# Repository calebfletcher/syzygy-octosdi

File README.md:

# syzygy-octosdi

SYZYGY™ TXR4 Compatible 3G-SDI Pod, with quad inputs and quad outputs.

Compatible with the SYZYGY Specification Version 1.1.1. The "SYZYGY™" mark is owned by Opal Kelly.

## Features
- SYZYGY TXR4 Pod
- 4x 3D-SDI inputs and 4x 3G-SDI outputs, all independent
- Full-size BNC connectors
- TI LMH0344 Cable Equalizers
- Semtech GS2988 Cable Drivers
- Lock/Signal Present LEDs at each BNC
- 148.5MHz oscillator on REFCLK
- I2C I/O expanders for all driver/equalizer control and status signals
- SmartVIO STM32G031 microcontroller with ability to measure VIO voltage

## Limitations
- Only 3G-SDI is supported
- There is no 148.5/1.001 MHz oscillator support
  - The board has only been designed for fractional framerates to keep the design a bit simpler. Depending on your FPGA, there may be enough tolerance on the MGT PLL to allow fractional rate inputs to be received despite it not being the correct frequency. This is the case at least for Xilinx Ultrascale+ GTYs with a +/-1250 ppm tolerance. However, this will not work for the transmitters which require the exact frequency.
- No reclockers on the board. It is designed to be plugged directly into an FPGA so this likely has no impact on its use.

## BOM Substitutions
While this board has been designed to use LMH0344 for the cable EQs and GS2988 for the cable drivers, there is broad compatibility across Semtech and TIs SDI portfolio. As such, some unpopulated footprints are available for passives needed for one chip or another, in particular for replacing the GS2988 with a LMH0302. See TI's SNLA280 for a full list of available substitutes for cable drivers, and SNLA283 for cable equalizers.

## [Interactive BOM](https://html-preview.github.io/?url=https://github.com/calebfletcher/syzygy-octosdi/blob/main/docs/ibom.html)

## Ordering Details
Designed to meet JLCPCBs standard capabilities.

Four layers, 1.6 mm, 1 oz outer/0.5 oz inner, JLC04161H-7628 stackup, controlled impedance.

## SYZYGY Compatibility Table

Following the pod compatibility table in [Appendix A of the SYZYGY Specification Version 1.1.1](https://syzygyfpga.io/wp-content/uploads/2023/09/Syzygy-Specification-V1p1p1.pdf):

| Parameter | syzygy-octosdi |
|-----------|----------------|
| Type | SYZYGY Transceiver (TXR-4) |
| Maximum 5V supply current | 0 mA |
| Maximum 3.3V supply current | 1.2 A (provisional design budget) |
| VIO supply voltage(s) | 1.8 V, 2.5 V, or 3.3 V |
| Maximum VIO supply current | 10 mA (provisional design budget) |
| Total number of I/O | 4 single-ended (S0–S3) |
| Number of differential I/O pairs (Standard pod only) | N/A (TXR-4 pod) |
| Transceiver lanes | 4 RX and 4 TX, plus REFCLK input |
| Width | Single |

The current budgets are conservative estimates from the schematic and component specifications; they have not been verified by measurement. The 5V pin is routed only to a test point. VIO powers the I/O side of the two expanders and the control-signal pull-ups.

## SYZYGY Pinout
Pinout for CN1 (QTH-020-01-F-D-DP-A):

| Pin number | Pin name      | Pin net      |
|------------|---------------|--------------|
| 01         | SCL\_01       | VIO\_I2C.SCL |
| 02         | +5V\_02       | +5V          |
| 03         | SDA\_03       | VIO\_I2C.SDA |
| 04         | R\_GA\_04     | R\_GA        |
| 05         | RX0P\_05      | RX0.P        |
| 06         | TX0P\_06      | TX0.P        |
| 07         | RX0N\_07      | RX0.N        |
| 08         | TX0N\_08      | TX0.N        |
| 09         | RX1P\_09      | RX1.P        |
| 10         | TX1P\_10      | TX1.P        |
| 11         | RX1N\_11      | RX1.N        |
| 12         | TX1N\_12      | TX1.N        |
| 13         | REFCLKP\_13   | REFCLK.P     |
| 14         | S0\_14        | I2C.SCL      |
| 15         | REFCLKN\_15   | REFCLK.N     |
| 16         | S1\_16        | I2C.SDA      |
| 17         | S2\_17        | ~{RESET}     |
| 18         | S3\_18        | ~{INT}       |
| 19         | S4\_19        | NC           |
| 20         | S5\_20        | NC           |
| 21         | S6\_21        | NC           |
| 22         | S7\_22        | NC           |
| 23         | S8\_23        | NC           |
| 24         | S9\_24        | NC           |
| 25         | RX3P\_25      | RX3.P        |
| 26         | TX3P\_26      | TX3.P        |
| 27         | RX3N\_27      | RX3.N        |
| 28         | TX3N\_28      | TX3.N        |
| 29         | RX2P\_29      | RX2.P        |
| 30         | TX2P\_30      | TX2.P        |
| 31         | RX2N\_31      | RX2.N        |
| 32         | TX2N\_32      | TX2.N        |
| 33         | P2C\_CLKP\_33 | NC           |
| 34         | C2P\_CLKP\_34 | NC           |
| 35         | P2C\_CLKN\_35 | NC           |
| 36         | C2P\_CLKN\_36 | NC           |
| 37         | RSVD\_37      | NC           |
| 38         | RSVD\_38      | NC           |
| 39         | VIO1\_39      | VIO          |
| 40         | +3.3V\_40     | +3V3         |
| G1         | GND\_G1       | GND          |
| G2         | GND\_G2       | GND          |
| G3         | GND\_G3       | GND          |
| G4         | GND\_G4       | GND          |

## SmartVIO STM32 Pinout
Pinout for U11 (STM32G031G8Ux):

| Pin number | Pin name       | Pin net               |
|------------|----------------|-----------------------|
| 1          | PC14\_1        | NC                    |
| 2          | PC15\_2        | NC                    |
| 3          | VDD\_3         | +3V3                  |
| 4          | VSS\_4         | GND                   |
| 5          | PF2\_5         | SmartVIO/NRST         |
| 6          | ADC1\_IN0\_6   | R\_GA                 |
| 7          | ADC1\_IN1\_7   | VIO                   |
| 8          | PA2\_8         | VIO\_GOOD             |
| 9          | PA3\_9         | ~{VIO\_GOOD}          |
| 10         | PA4\_10        | NC                    |
| 11         | PA5\_11        | NC                    |
| 12         | PA6\_12        | NC                    |
| 13         | PA7\_13        | NC                    |
| 14         | PB0\_14        | Net-(U11-PB0)         |
| 15         | PB1\_15        | Net-(U11-PB1)         |
| 16         | PA8\_16        | NC                    |
| 17         | PC6\_17        | NC                    |
| 18         | PA9/PA11\_18   | NC                    |
| 19         | PA10/PA12\_19  | NC                    |
| 20         | SYS\_SWDIO\_20 | SmartVIO/SWDIO        |
| 21         | SYS\_SWCLK\_21 | SmartVIO/SWCLK        |
| 22         | PA15\_22       | NC                    |
| 23         | PB3\_23        | NC                    |
| 24         | PB4\_24        | SmartVIO/USER\_LED\_0 |
| 25         | PB5\_25        | SmartVIO/USER\_LED\_1 |
| 26         | I2C1\_SCL\_26  | VIO\_I2C.SCL          |
| 27         | I2C1\_SDA\_27  | VIO\_I2C.SDA          |
| 28         | PB8\_28        | NC                    |

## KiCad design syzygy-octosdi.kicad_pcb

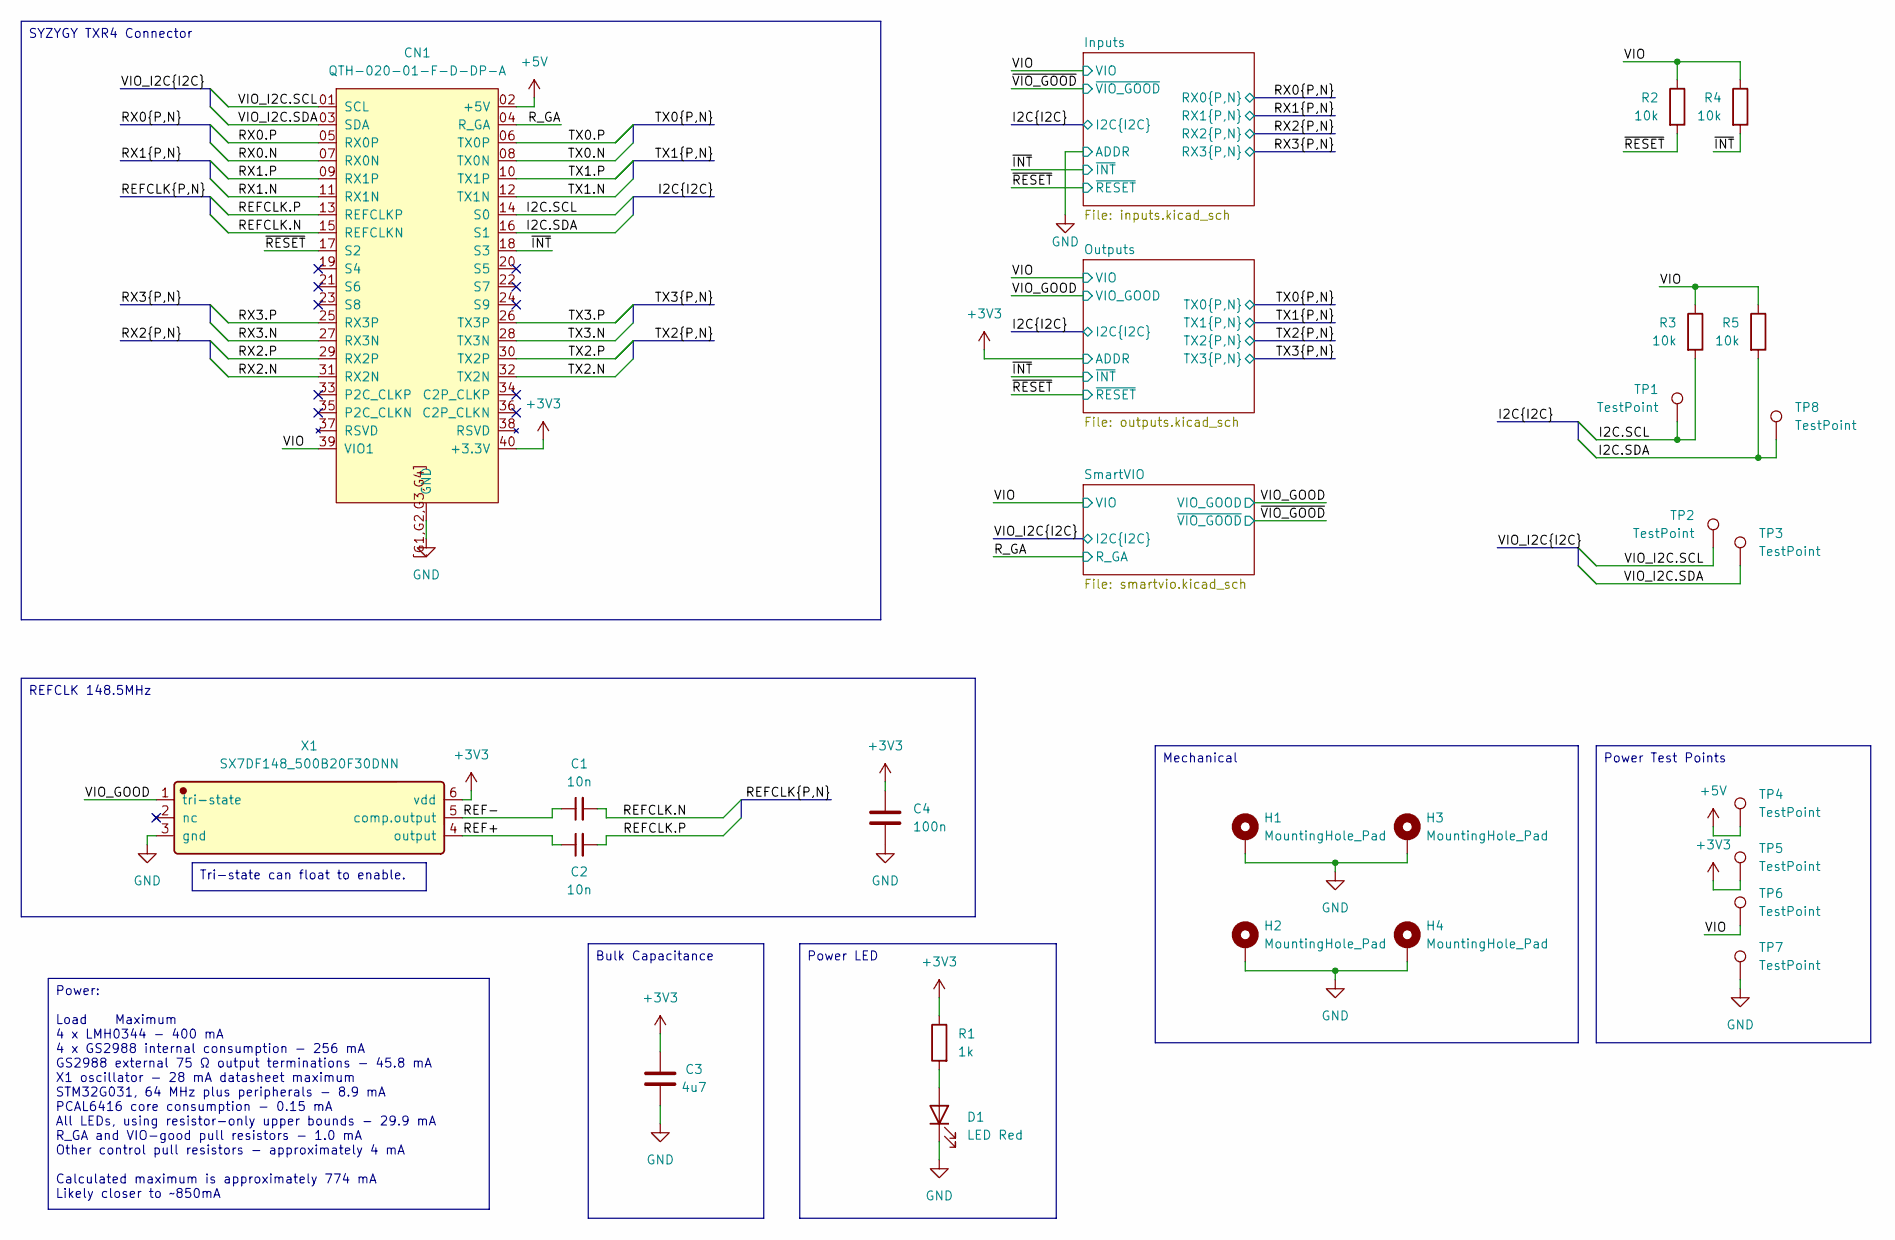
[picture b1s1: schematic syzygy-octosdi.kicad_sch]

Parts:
C1, C2: 10n; C_0402_1005Metric; LCSC C15195
C3: 4u7; C_0603_1608Metric; LCSC C69335
C4: 100n; C_0603_1608Metric; LCSC C282519
CN1: QTH-020-01-F-D-DP-A; Manufacturer Part QTH-020-01-F-D-DP-A; LCSC C5852101
D1: LED Red; LED_0603_1608Metric; LCSC C965799
H1, H2, H3, H4: MountingHole_Pad; MountingHole_3.2mm_M3_Pad
R1: 1k; R_0603_1608Metric; LCSC C21190
R2, R3, R4, R5: 10k; R_0603_1608Metric; LCSC C25804
TP1, TP2, TP3, TP4, TP5, TP6, TP7, TP8: TestPoint; TestPoint_Pad_D1.0mm
X1: SX7DF148_500B20F30DNN; Manufacturer Part SX7DF148.500B20F30DNN; LCSC C5179986

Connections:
+3V3: C3.1, C4.1, CN1.40 (+3.3V), R1.1, TP5.1 (1_1), X1.6 (vdd); also elsewhere on the board
+5V: CN1.02 (+5V), TP4.1 (1_1)
/I2C.SCL: CN1.14 (S0), R3.2, TP1.1 (1_1); also elsewhere on the board
/I2C.SDA: CN1.16 (S1), R5.2, TP8.1 (1_1); also elsewhere on the board
/REF+: C2.1, X1.4 (output)
/REF-: C1.1, X1.5 (comp.output)
/REFCLK.N: C1.2, CN1.15 (REFCLKN)
/REFCLK.P: C2.2, CN1.13 (REFCLKP)
/RX0.N: CN1.07 (RX0N); also elsewhere on the board
/RX0.P: CN1.05 (RX0P); also elsewhere on the board
/RX1.N: CN1.11 (RX1N); also elsewhere on the board
/RX1.P: CN1.09 (RX1P); also elsewhere on the board
/RX2.N: CN1.31 (RX2N); also elsewhere on the board
/RX2.P: CN1.29 (RX2P); also elsewhere on the board
/RX3.N: CN1.27 (RX3N); also elsewhere on the board
/RX3.P: CN1.25 (RX3P); also elsewhere on the board
/R_GA: CN1.04 (R_GA); also elsewhere on the board
/TX0.N: CN1.08 (TX0N); also elsewhere on the board
/TX0.P: CN1.06 (TX0P); also elsewhere on the board
/TX1.N: CN1.12 (TX1N); also elsewhere on the board
/TX1.P: CN1.10 (TX1P); also elsewhere on the board
/TX2.N: CN1.32 (TX2N); also elsewhere on the board
/TX2.P: CN1.30 (TX2P); also elsewhere on the board
/TX3.N: CN1.28 (TX3N); also elsewhere on the board
/TX3.P: CN1.26 (TX3P); also elsewhere on the board
/VIO: CN1.39 (VIO1), R2.1, R3.1, R4.1, R5.1, TP6.1 (1_1); also elsewhere on the board
/VIO_GOOD: X1.1 (tri-state); also elsewhere on the board
/VIO_I2C.SCL: CN1.01 (SCL), TP2.1 (1_1); also elsewhere on the board
/VIO_I2C.SDA: CN1.03 (SDA), TP3.1 (1_1); also elsewhere on the board
/~INT: CN1.18 (S3), R4.2; also elsewhere on the board
/~RESET: CN1.17 (S2), R2.2; also elsewhere on the board
GND: C3.2, C4.2, CN1.G1 (GND), CN1.G2 (GND), CN1.G3 (GND), CN1.G4 (GND), CN1.[G1,G2,G3,G4] (GND), D1.1 (K), H1.1 (1_1), H2.1 (1_1), H3.1 (1_1), H4.1 (1_1), TP7.1 (1_1), X1.3 (gnd); also elsewhere on the board
unnamed: D1.2 (A), R1.2

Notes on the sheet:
Power: Load Maximum 4 x LMH0344 - 400 mA 4 x GS2988 internal consumption - 256 mA GS2988 external 75 Ω output terminations - 45.8 mA X1 oscillator - 28 mA datasheet maximum STM32G031, 64 MHz plus peripherals - 8.9 mA PCAL6416 core consumption - 0.15 mA All LEDs, using resistor-only upper bounds - 2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
Mechanical
SYZYGY TXR4 Connector
Power Test Points
REFCLK 148.5MHz
Bulk Capacitance
Tri-state can float to enable.
Power LED

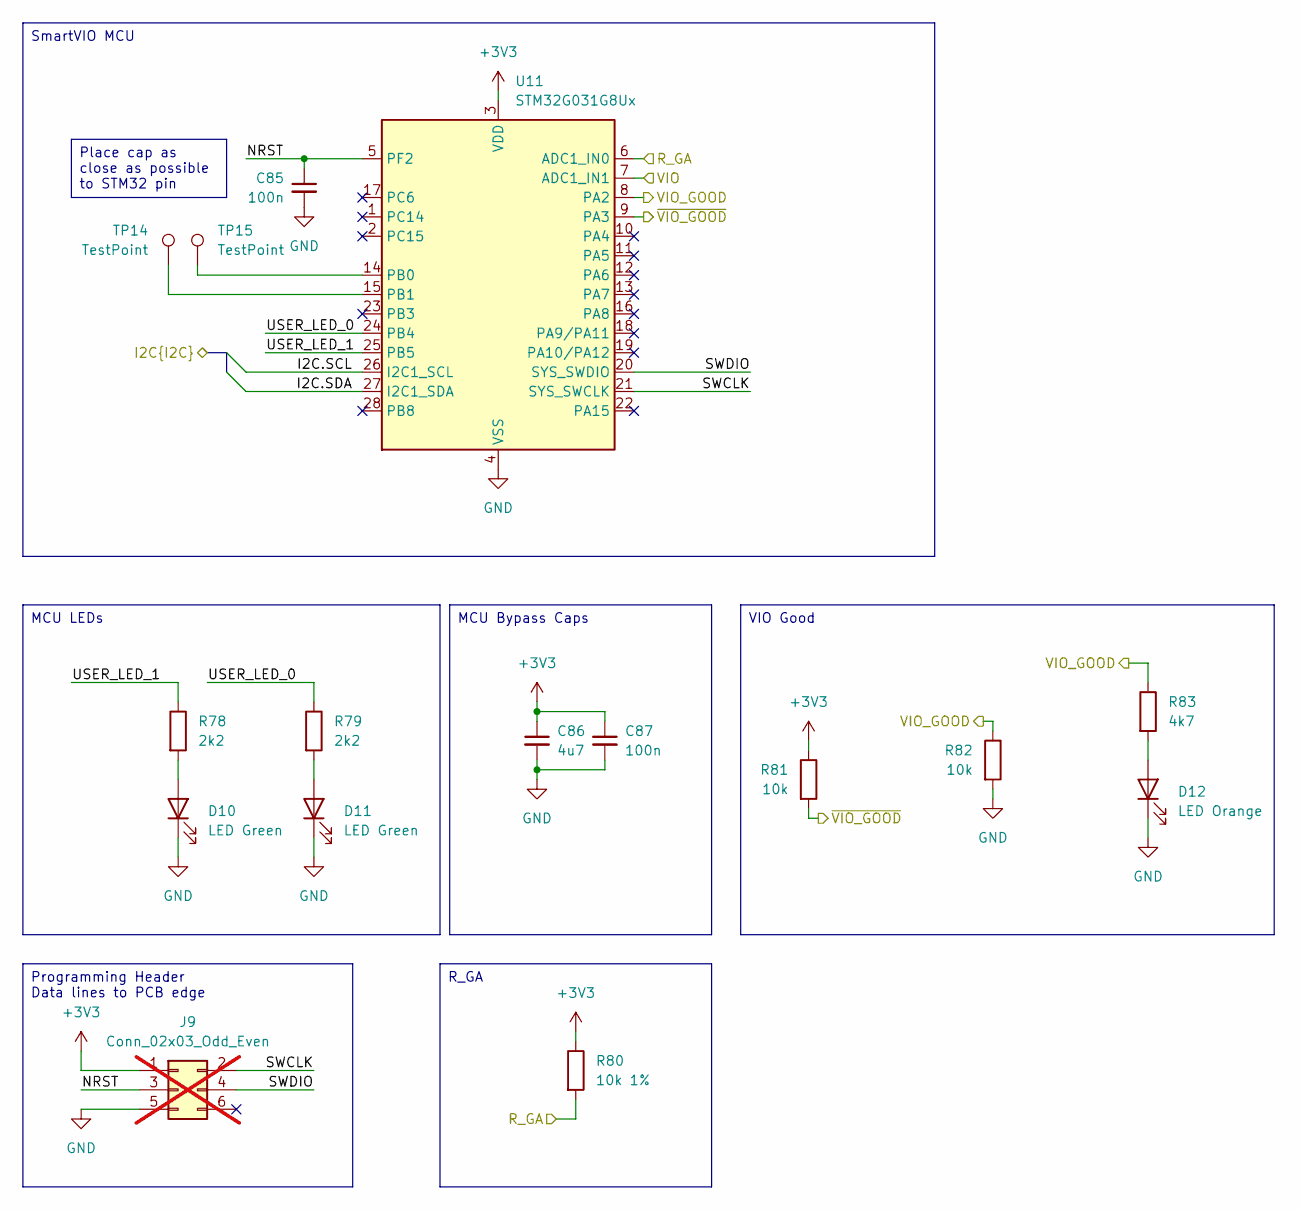
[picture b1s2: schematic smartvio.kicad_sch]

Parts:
C85, C87: 100n; C_0603_1608Metric; LCSC C282519
C86: 4u7; C_0603_1608Metric; LCSC C69335
D10, D11: LED Green; LED_0603_1608Metric; LCSC C965804
D12: LED Orange; LED_0603_1608Metric; LCSC C965800
J9: Conn_02x03_Odd_Even; PinHeader_2x03_P1.27mm_Vertical; not fitted
R78, R79: 2k2; R_0603_1608Metric; LCSC C2907005
R80: 10k 1%; R_0603_1608Metric; LCSC C25804
R81, R82: 10k; R_0603_1608Metric; LCSC C25804
R83: 4k7; R_0603_1608Metric; LCSC C2907034
TP14, TP15: TestPoint; TestPoint_Pad_D1.0mm
U11: STM32G031G8Ux; UFQFPN-28_STM; LCSC C432211

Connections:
+3V3: C86.1, C87.1, J9.1, R80.1, R81.1, U11.3 (VDD); also elsewhere on the board
/R_GA: R80.2, U11.6 (ADC1_IN0); also elsewhere on the board
/SmartVIO/NRST: C85.1, J9.3, U11.5 (PF2)
/SmartVIO/SWCLK: J9.2, U11.21 (SYS_SWCLK)
/SmartVIO/SWDIO: J9.4, U11.20 (SYS_SWDIO)
/SmartVIO/USER_LED_0: R79.1, U11.24 (PB4)
/SmartVIO/USER_LED_1: R78.1, U11.25 (PB5)
/VIO: U11.7 (ADC1_IN1); also elsewhere on the board
/VIO_GOOD: R82.1, R83.1, U11.8 (PA2); also elsewhere on the board
/VIO_I2C.SCL: U11.26 (I2C1_SCL); also elsewhere on the board
/VIO_I2C.SDA: U11.27 (I2C1_SDA); also elsewhere on the board
/~VIO_GOOD: R81.2, U11.9 (PA3); also elsewhere on the board
GND: C85.2, C86.2, C87.2, D10.1 (K), D11.1 (K), D12.1 (K), J9.5, R82.2, U11.4 (VSS); also elsewhere on the board
unnamed: D10.2 (A), R78.2
unnamed: D11.2 (A), R79.2
unnamed: D12.2 (A), R83.2
unnamed: TP15.1 (1_1), U11.14 (PB0)
unnamed: TP14.1 (1_1), U11.15 (PB1)

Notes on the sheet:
MCU Bypass Caps
VIO Good
MCU LEDs
Programming Header Data lines to PCB edge
Place cap as close as possible to STM32 pin
SmartVIO MCU
R_GA

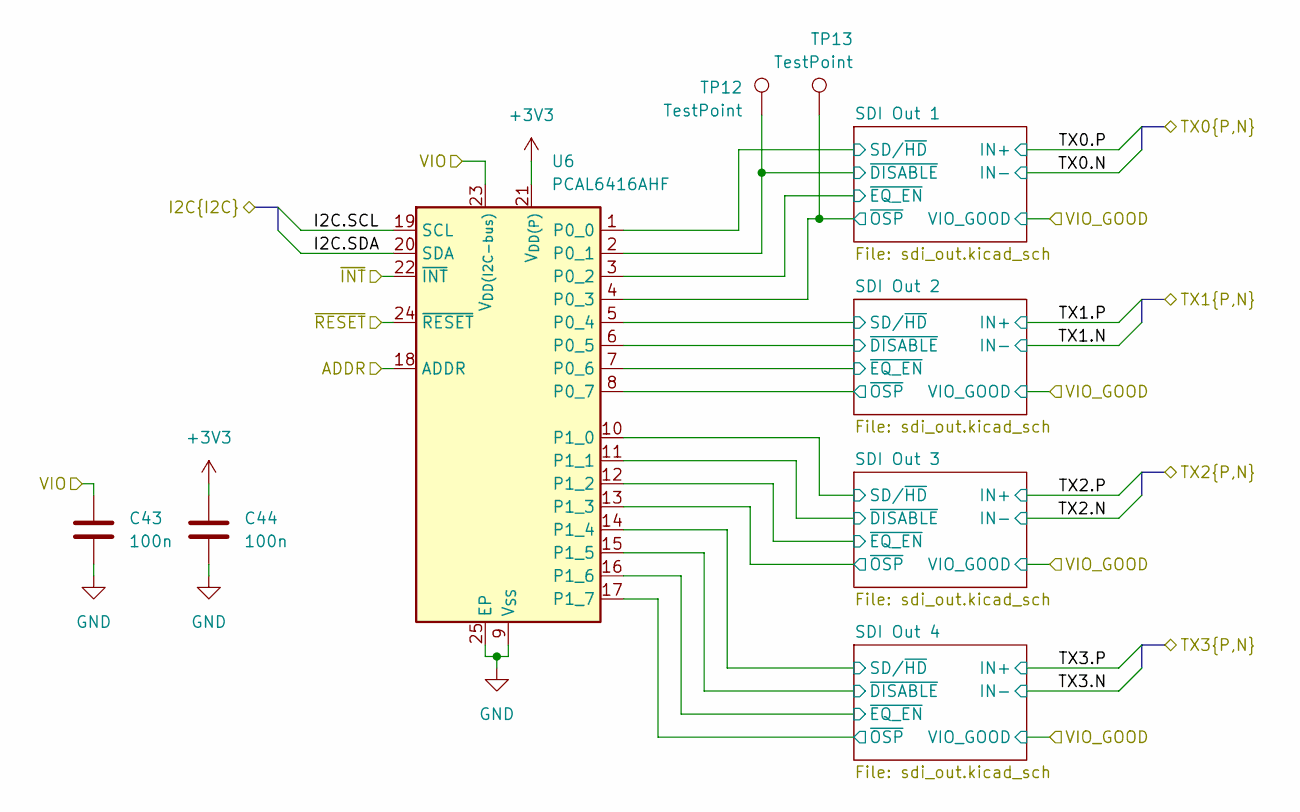
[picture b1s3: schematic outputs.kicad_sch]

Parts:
C43, C44: 100n; C_0402_1005Metric; LCSC C1525
TP12, TP13: TestPoint; TestPoint_Pad_D1.0mm
U6: PCAL6416AHF; HVQFN-24-1EP_4x4mm_P0.5mm_EP2.1x2.1mm; LCSC C2652287

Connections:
+3V3: C44.1, U6.18 (ADDR), U6.21 (V_{DD(P)}); also elsewhere on the board
/I2C.SCL: U6.19 (SCL); also elsewhere on the board
/I2C.SDA: U6.20 (SDA); also elsewhere on the board
/Outputs/SDI Out 1/SD/~HD: U6.1 (P0_0); also elsewhere on the board
/Outputs/SDI Out 1/~DISABLE: TP12.1 (1_1), U6.2 (P0_1); also elsewhere on the board
/Outputs/SDI Out 1/~EQ_EN: U6.3 (P0_2); also elsewhere on the board
/Outputs/SDI Out 1/~OSP: TP13.1 (1_1), U6.4 (P0_3); also elsewhere on the board
/Outputs/SDI Out 2/SD/~HD: U6.5 (P0_4); also elsewhere on the board
/Outputs/SDI Out 2/~DISABLE: U6.6 (P0_5); also elsewhere on the board
/Outputs/SDI Out 2/~EQ_EN: U6.7 (P0_6); also elsewhere on the board
/Outputs/SDI Out 2/~OSP: U6.8 (P0_7); also elsewhere on the board
/Outputs/SDI Out 3/SD/~HD: U6.10 (P1_0); also elsewhere on the board
/Outputs/SDI Out 3/~DISABLE: U6.11 (P1_1); also elsewhere on the board
/Outputs/SDI Out 3/~EQ_EN: U6.12 (P1_2); also elsewhere on the board
/Outputs/SDI Out 3/~OSP: U6.13 (P1_3); also elsewhere on the board
/Outputs/SDI Out 4/SD/~HD: U6.14 (P1_4); also elsewhere on the board
/Outputs/SDI Out 4/~DISABLE: U6.15 (P1_5); also elsewhere on the board
/Outputs/SDI Out 4/~EQ_EN: U6.16 (P1_6); also elsewhere on the board
/Outputs/SDI Out 4/~OSP: U6.17 (P1_7); also elsewhere on the board
/VIO: C43.1, U6.23 (V_{DD(I2C-bus)}); also elsewhere on the board
/~INT: U6.22 (~INT); also elsewhere on the board
/~RESET: U6.24 (~RESET); also elsewhere on the board
GND: C43.2, C44.2, U6.9 (V_{SS}), U6.25 (EP); also elsewhere on the board

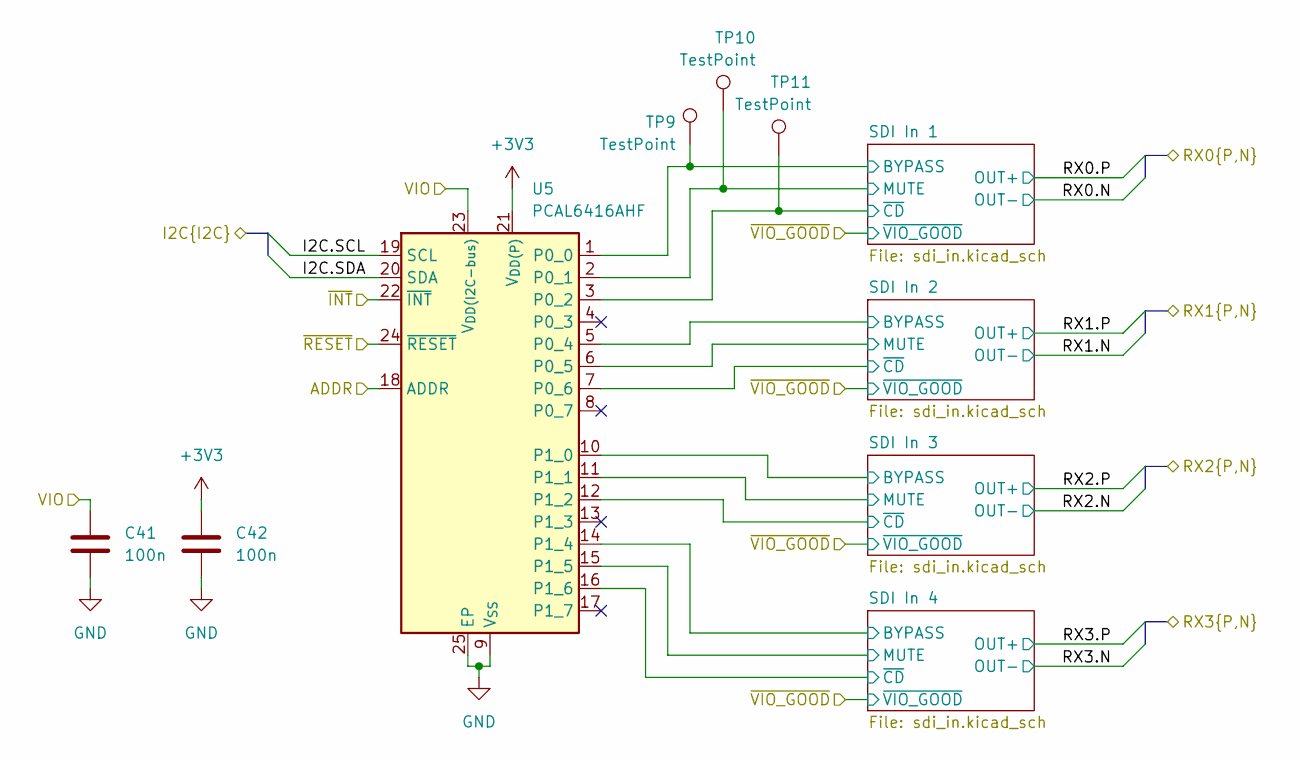
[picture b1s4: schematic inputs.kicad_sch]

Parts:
C41, C42: 100n; C_0402_1005Metric; LCSC C1525
TP9, TP10, TP11: TestPoint; TestPoint_Pad_D1.0mm
U5: PCAL6416AHF; HVQFN-24-1EP_4x4mm_P0.5mm_EP2.1x2.1mm; LCSC C2652287

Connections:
+3V3: C42.1, U5.21 (V_{DD(P)}); also elsewhere on the board
/I2C.SCL: U5.19 (SCL); also elsewhere on the board
/I2C.SDA: U5.20 (SDA); also elsewhere on the board
/Inputs/SDI In 1/BYPASS: TP9.1 (1_1), U5.1 (P0_0); also elsewhere on the board
/Inputs/SDI In 1/MUTE: TP10.1 (1_1), U5.2 (P0_1); also elsewhere on the board
/Inputs/SDI In 1/~CD: TP11.1 (1_1), U5.3 (P0_2); also elsewhere on the board
/Inputs/SDI In 2/BYPASS: U5.5 (P0_4); also elsewhere on the board
/Inputs/SDI In 2/MUTE: U5.6 (P0_5); also elsewhere on the board
/Inputs/SDI In 2/~CD: U5.7 (P0_6); also elsewhere on the board
/Inputs/SDI In 3/BYPASS: U5.10 (P1_0); also elsewhere on the board
/Inputs/SDI In 3/MUTE: U5.11 (P1_1); also elsewhere on the board
/Inputs/SDI In 3/~CD: U5.12 (P1_2); also elsewhere on the board
/Inputs/SDI In 4/BYPASS: U5.14 (P1_4); also elsewhere on the board
/Inputs/SDI In 4/MUTE: U5.15 (P1_5); also elsewhere on the board
/Inputs/SDI In 4/~CD: U5.16 (P1_6); also elsewhere on the board
/VIO: C41.1, U5.23 (V_{DD(I2C-bus)}); also elsewhere on the board
/~INT: U5.22 (~INT); also elsewhere on the board
/~RESET: U5.24 (~RESET); also elsewhere on the board
GND: C41.2, C42.2, U5.9 (V_{SS}), U5.18 (ADDR), U5.25 (EP); also elsewhere on the board

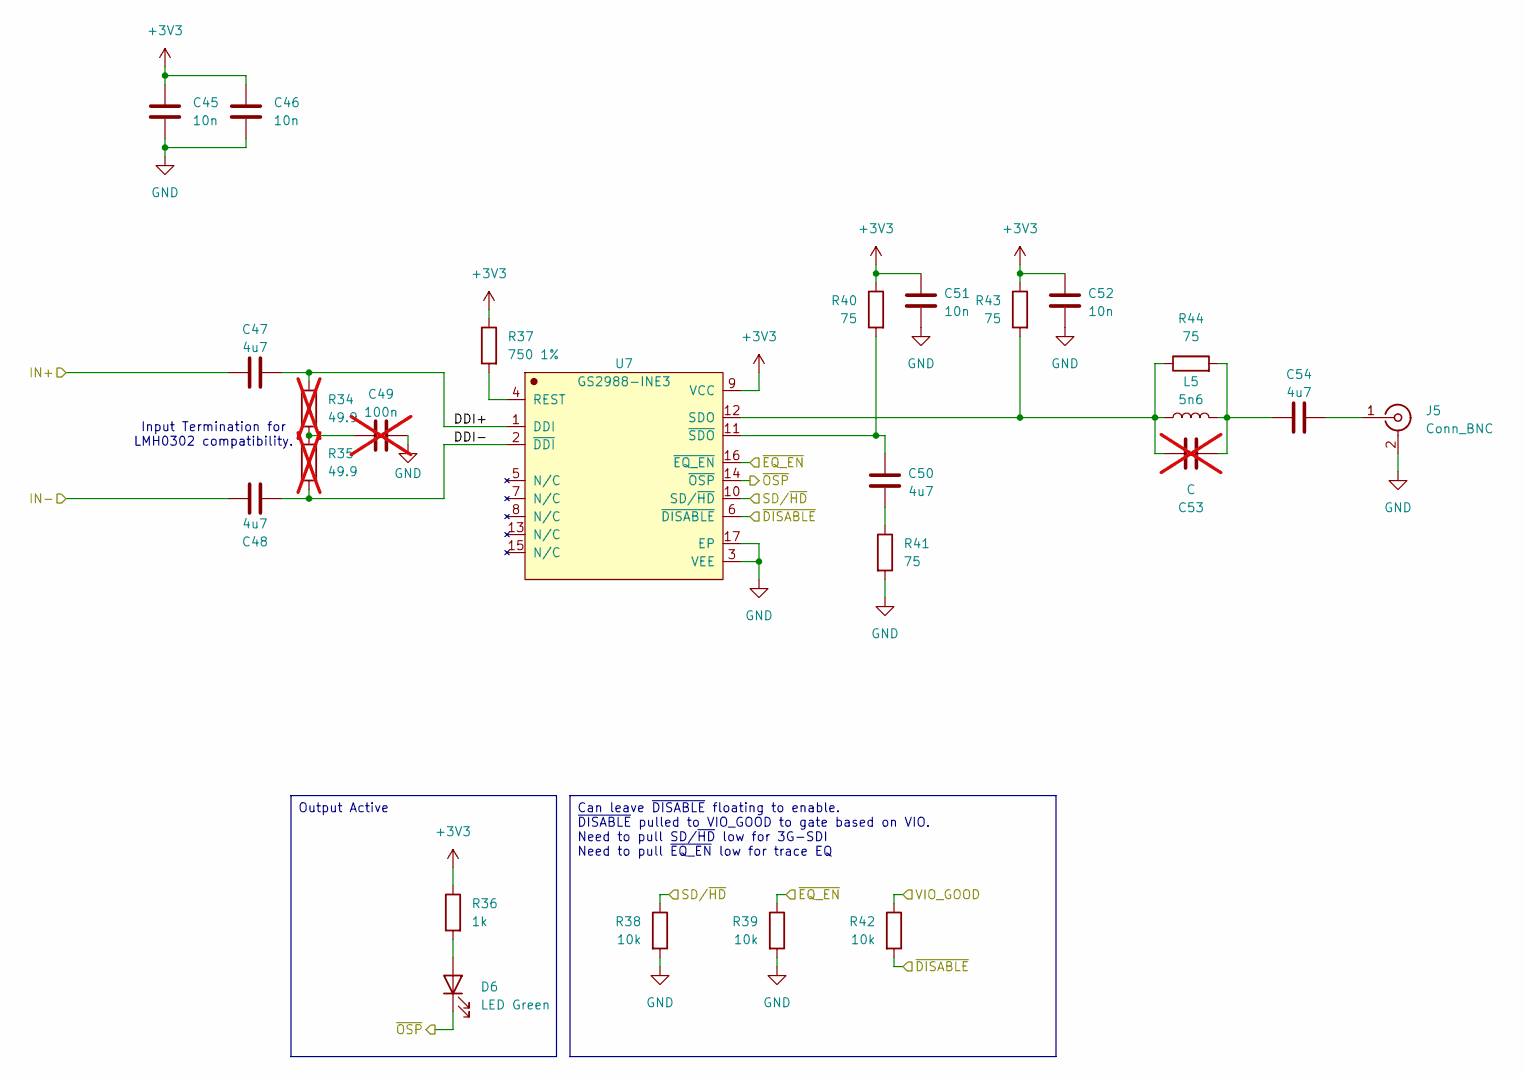
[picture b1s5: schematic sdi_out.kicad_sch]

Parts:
C45, C46, C51, C52: 10n; C_0402_1005Metric; LCSC C15195
C47, C48, C50, C54: 4u7; C_0603_1608Metric; LCSC C69335
C49: 100n; C_0402_1005Metric; LCSC C1525; not fitted
C53: C; C_0402_1005Metric; not fitted
D6: LED Green; LED_0603_1608Metric; LCSC C965804
J5: Conn_BNC; CONN_73171-1900_MOL; Manufacturer Part 731711900
L5: 5n6; L_0402_1005Metric; LCSC C3223990
R34, R35: 49.9; R_0402_1005Metric; not fitted
R36: 1k; R_0603_1608Metric; LCSC C21190
R37: 750 1%; R_0603_1608Metric; LCSC C118388
R38, R39, R42: 10k; R_0603_1608Metric; LCSC C25804
R40, R41, R43, R44: 75; R_0402_1005Metric; LCSC C324774
U7: GS2988-INE3; Manufacturer Part GS2988-INE3; LCSC C5367442

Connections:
+3V3: C45.1, C46.1, C51.1, C52.1, R36.1, R37.1, R40.1, R43.1, U7.9 (VCC); also elsewhere on the board
/Outputs/SDI Out 1/DDI+: C47.2, R34.1, U7.1 (DDI)
/Outputs/SDI Out 1/DDI-: C48.2, R35.2, U7.2 (~DDI)
/Outputs/SDI Out 1/SD/~HD: R38.1, U7.10 (SD/~HD); also elsewhere on the board
/Outputs/SDI Out 1/~DISABLE: R42.2, U7.6 (~DISABLE); also elsewhere on the board
/Outputs/SDI Out 1/~EQ_EN: R39.1, U7.16 (~EQ_EN); also elsewhere on the board
/Outputs/SDI Out 1/~OSP: D6.1 (K), U7.14 (~OSP); also elsewhere on the board
/TX0.N: C48.1; also elsewhere on the board
/TX0.P: C47.1; also elsewhere on the board
/VIO_GOOD: R42.1; also elsewhere on the board
GND: C45.2, C46.2, C49.2, C51.2, C52.2, J5.2 (Ext), R38.2, R39.2, R41.2, U7.3 (VEE), U7.17 (EP); also elsewhere on the board
unnamed: C49.1, R34.2, R35.1
unnamed: C50.2, R41.1
unnamed: C53.2, C54.1, L5.2, R44.2
unnamed: D6.2 (A), R36.2
unnamed: C54.2, J5.1 (In)
unnamed: R37.2, U7.4 (REST)
unnamed: C53.1, L5.1, R43.2, R44.1, U7.12 (SDO)
unnamed: C50.1, R40.2, U7.11 (~SDO)

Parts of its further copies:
C55, C56, C61, C62, C65, C66, C71, C72, C75, C76, C81, C82: 10n; C_0402_1005Metric; LCSC C15195
C57, C58, C60, C64, C67, C68, C70, C74, C77, C78, C80, C84: 4u7; C_0603_1608Metric; LCSC C69335
C59, C69, C79: 100n; C_0402_1005Metric; LCSC C1525; not fitted
C63, C73, C83: C; C_0402_1005Metric; not fitted
D7, D8, D9: LED Green; LED_0603_1608Metric; LCSC C965804
J6, J7, J8: Conn_BNC; CONN_73171-1900_MOL; Manufacturer Part 731711900
L6, L7, L8: 5n6; L_0402_1005Metric; LCSC C3223990
R45, R46, R56, R57, R67, R68: 49.9; R_0402_1005Metric; not fitted
R47, R58, R69: 1k; R_0603_1608Metric; LCSC C21190
R48, R59, R70: 750 1%; R_0603_1608Metric; LCSC C118388
R49, R50, R53, R60, R61, R64, R71, R72, R75: 10k; R_0603_1608Metric; LCSC C25804
R51, R52, R54, R55, R62, R63, R65, R66, R73, R74, R76, R77: 75; R_0402_1005Metric; LCSC C324774
U8, U9, U10: GS2988-INE3; Manufacturer Part GS2988-INE3; LCSC C5367442

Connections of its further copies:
+3V3: C55.1, C56.1, C61.1, C62.1, C65.1, C66.1, C71.1, C72.1, C75.1, C76.1, C81.1, C82.1, R47.1, R48.1, R51.1, R54.1, R58.1, R59.1, R62.1, R65.1, R69.1, R70.1, R73.1, R76.1, U8.9 (VCC), U9.9 (VCC), U10.9 (VCC); also elsewhere on the board
/Outputs/SDI Out 2/DDI+: C57.2, R45.1, U8.1 (DDI)
/Outputs/SDI Out 2/DDI-: C58.2, R46.2, U8.2 (~DDI)
/Outputs/SDI Out 2/SD/~HD: R49.1, U8.10 (SD/~HD); also elsewhere on the board
/Outputs/SDI Out 2/~DISABLE: R53.2, U8.6 (~DISABLE); also elsewhere on the board
/Outputs/SDI Out 2/~EQ_EN: R50.1, U8.16 (~EQ_EN); also elsewhere on the board
/Outputs/SDI Out 2/~OSP: D7.1 (K), U8.14 (~OSP); also elsewhere on the board
/Outputs/SDI Out 3/DDI+: C67.2, R56.1, U9.1 (DDI)
/Outputs/SDI Out 3/DDI-: C68.2, R57.2, U9.2 (~DDI)
/Outputs/SDI Out 3/SD/~HD: R60.1, U9.10 (SD/~HD); also elsewhere on the board
/Outputs/SDI Out 3/~DISABLE: R64.2, U9.6 (~DISABLE); also elsewhere on the board
/Outputs/SDI Out 3/~EQ_EN: R61.1, U9.16 (~EQ_EN); also elsewhere on the board
/Outputs/SDI Out 3/~OSP: D8.1 (K), U9.14 (~OSP); also elsewhere on the board
/Outputs/SDI Out 4/DDI+: C77.2, R67.1, U10.1 (DDI)
/Outputs/SDI Out 4/DDI-: C78.2, R68.2, U10.2 (~DDI)
/Outputs/SDI Out 4/SD/~HD: R71.1, U10.10 (SD/~HD); also elsewhere on the board
/Outputs/SDI Out 4/~DISABLE: R75.2, U10.6 (~DISABLE); also elsewhere on the board
/Outputs/SDI Out 4/~EQ_EN: R72.1, U10.16 (~EQ_EN); also elsewhere on the board
/Outputs/SDI Out 4/~OSP: D9.1 (K), U10.14 (~OSP); also elsewhere on the board
/TX1.N: C58.1; also elsewhere on the board
/TX1.P: C57.1; also elsewhere on the board
/TX2.N: C68.1; also elsewhere on the board
/TX2.P: C67.1; also elsewhere on the board
/TX3.N: C78.1; also elsewhere on the board
/TX3.P: C77.1; also elsewhere on the board
/VIO_GOOD: R53.1, R64.1, R75.1; also elsewhere on the board
GND: C55.2, C56.2, C59.2, C61.2, C62.2, C65.2, C66.2, C69.2, C71.2, C72.2, C75.2, C76.2, C79.2, C81.2, C82.2, J6.2 (Ext), J7.2 (Ext), J8.2 (Ext), R49.2, R50.2, R52.2, R60.2, R61.2, R63.2, R71.2, R72.2, R74.2, U8.3 (VEE), U8.17 (EP), U9.3 (VEE), U9.17 (EP), U10.3 (VEE), U10.17 (EP); also elsewhere on the board
unnamed: C59.1, R45.2, R46.1
unnamed: C60.2, R52.1
unnamed: C63.2, C64.1, L6.2, R55.2
unnamed: C69.1, R56.2, R57.1
unnamed: C70.2, R63.1
unnamed: C73.2, C74.1, L7.2, R66.2
unnamed: C79.1, R67.2, R68.1
unnamed: C80.2, R74.1
unnamed: C83.2, C84.1, L8.2, R77.2
unnamed: D7.2 (A), R47.2
unnamed: D8.2 (A), R58.2
unnamed: D9.2 (A), R69.2
unnamed: C64.2, J6.1 (In)
unnamed: C74.2, J7.1 (In)
unnamed: C84.2, J8.1 (In)
unnamed: R48.2, U8.4 (REST)
unnamed: C63.1, L6.1, R54.2, R55.1, U8.12 (SDO)
unnamed: C60.1, R51.2, U8.11 (~SDO)
unnamed: R59.2, U9.4 (REST)
unnamed: C73.1, L7.1, R65.2, R66.1, U9.12 (SDO)
unnamed: C70.1, R62.2, U9.11 (~SDO)
unnamed: R70.2, U10.4 (REST)
unnamed: C83.1, L8.1, R76.2, R77.1, U10.12 (SDO)
unnamed: C80.1, R73.2, U10.11 (~SDO)

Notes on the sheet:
Input Termination for LMH0302 compatibility.
Output Active
Can leave ~{DISABLE} floating to enable. ~{DISABLE} pulled to VIO_GOOD to gate based on VIO. Need to pull SD/~{HD} low for 3G-SDI Need to pull ~{EQ_EN} low for trace EQ

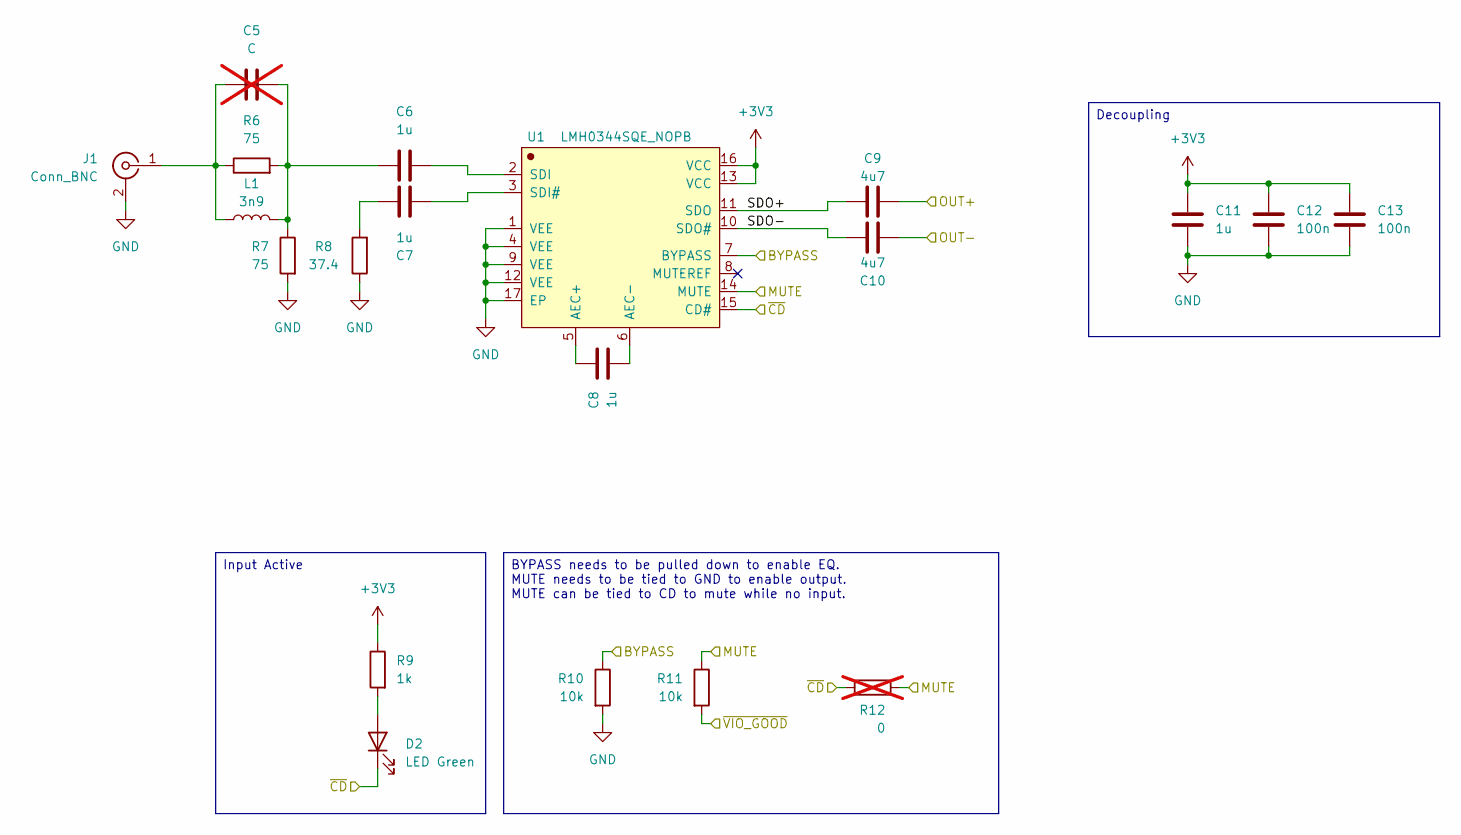
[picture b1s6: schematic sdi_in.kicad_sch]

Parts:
C5: C; C_0402_1005Metric; not fitted
C6, C7: 1u; C_0402_1005Metric; LCSC C49210445
C8, C11: 1u; C_0603_1608Metric; LCSC C6119818
C9, C10: 4u7; C_0603_1608Metric; LCSC C69335
C12, C13: 100n; C_0603_1608Metric; LCSC C282519
D2: LED Green; LED_0603_1608Metric; LCSC C965804
J1: Conn_BNC; CONN_73171-1900_MOL; Manufacturer Part 731711900
L1: 3n9; L_0402_1005Metric; LCSC C412279
R6, R7: 75; R_0402_1005Metric; LCSC C324774
R8: 37.4; R_0402_1005Metric; LCSC C2091522
R9: 1k; R_0603_1608Metric; LCSC C21190
R10, R11: 10k; R_0603_1608Metric; LCSC C25804
R12: 0; R_0603_1608Metric; LCSC C15402; not fitted
U1: LMH0344SQE_NOPB; WQFN-16-1EP_4x4mm_P0.65mm_EP2.6x2.6mm_ThermalVias; Manufacturer Part LMH0344SQE/NOPB; LCSC C2652894

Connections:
+3V3: C11.1, C12.1, C13.1, R9.1, U1.13 (VCC), U1.16 (VCC); also elsewhere on the board
/Inputs/SDI In 1/BYPASS: R10.1, U1.7 (BYPASS); also elsewhere on the board
/Inputs/SDI In 1/MUTE: R11.1, R12.2, U1.14 (MUTE); also elsewhere on the board
/Inputs/SDI In 1/SDO+: C9.1, U1.11 (SDO)
/Inputs/SDI In 1/SDO-: C10.1, U1.10 (SDO#)
/Inputs/SDI In 1/~CD: D2.1 (K), R12.1, U1.15 (CD#); also elsewhere on the board
/RX0.N: C10.2; also elsewhere on the board
/RX0.P: C9.2; also elsewhere on the board
/~VIO_GOOD: R11.2; also elsewhere on the board
GND: C11.2, C12.2, C13.2, J1.2 (Ext), R7.2, R8.1, R10.2, U1.1 (VEE), U1.4 (VEE), U1.9 (VEE), U1.12 (VEE), U1.17 (EP); also elsewhere on the board
unnamed: C5.2, C6.1, L1.2, R6.2, R7.1
unnamed: C7.1, R8.2
unnamed: D2.2 (A), R9.2
unnamed: C5.1, J1.1 (In), L1.1, R6.1
unnamed: C8.1, U1.5 (AEC+)
unnamed: C8.2, U1.6 (AEC-)
unnamed: C7.2, U1.3 (SDI#)
unnamed: C6.2, U1.2 (SDI)

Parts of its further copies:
C14, C23, C32: C; C_0402_1005Metric; not fitted
C15, C16, C24, C25, C33, C34: 1u; C_0402_1005Metric; LCSC C49210445
C17, C20, C26, C29, C35, C38: 1u; C_0603_1608Metric; LCSC C6119818
C18, C19, C27, C28, C36, C37: 4u7; C_0603_1608Metric; LCSC C69335
C21, C22, C30, C31, C39, C40: 100n; C_0603_1608Metric; LCSC C282519
D3, D4, D5: LED Green; LED_0603_1608Metric; LCSC C965804
J2, J3, J4: Conn_BNC; CONN_73171-1900_MOL; Manufacturer Part 731711900
L2, L3, L4: 3n9; L_0402_1005Metric; LCSC C412279
R13, R14, R20, R21, R27, R28: 75; R_0402_1005Metric; LCSC C324774
R15, R22, R29: 37.4; R_0402_1005Metric; LCSC C2091522
R16, R23, R30: 1k; R_0603_1608Metric; LCSC C21190
R17, R18, R24, R25, R31, R32: 10k; R_0603_1608Metric; LCSC C25804
R19, R26, R33: 0; R_0603_1608Metric; LCSC C15402; not fitted
U2, U3, U4: LMH0344SQE_NOPB; WQFN-16-1EP_4x4mm_P0.65mm_EP2.6x2.6mm_ThermalVias; Manufacturer Part LMH0344SQE/NOPB; LCSC C2652894

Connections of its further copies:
+3V3: C20.1, C21.1, C22.1, C29.1, C30.1, C31.1, C38.1, C39.1, C40.1, R16.1, R23.1, R30.1, U2.13 (VCC), U2.16 (VCC), U3.13 (VCC), U3.16 (VCC), U4.13 (VCC), U4.16 (VCC); also elsewhere on the board
/Inputs/SDI In 2/BYPASS: R17.1, U2.7 (BYPASS); also elsewhere on the board
/Inputs/SDI In 2/MUTE: R18.1, R19.2, U2.14 (MUTE); also elsewhere on the board
/Inputs/SDI In 2/SDO+: C18.1, U2.11 (SDO)
/Inputs/SDI In 2/SDO-: C19.1, U2.10 (SDO#)
/Inputs/SDI In 2/~CD: D3.1 (K), R19.1, U2.15 (CD#); also elsewhere on the board
/Inputs/SDI In 3/BYPASS: R24.1, U3.7 (BYPASS); also elsewhere on the board
/Inputs/SDI In 3/MUTE: R25.1, R26.2, U3.14 (MUTE); also elsewhere on the board
/Inputs/SDI In 3/SDO+: C27.1, U3.11 (SDO)
/Inputs/SDI In 3/SDO-: C28.1, U3.10 (SDO#)
/Inputs/SDI In 3/~CD: D4.1 (K), R26.1, U3.15 (CD#); also elsewhere on the board
/Inputs/SDI In 4/BYPASS: R31.1, U4.7 (BYPASS); also elsewhere on the board
/Inputs/SDI In 4/MUTE: R32.1, R33.2, U4.14 (MUTE); also elsewhere on the board
/Inputs/SDI In 4/SDO+: C36.1, U4.11 (SDO)
/Inputs/SDI In 4/SDO-: C37.1, U4.10 (SDO#)
/Inputs/SDI In 4/~CD: D5.1 (K), R33.1, U4.15 (CD#); also elsewhere on the board
/RX1.N: C19.2; also elsewhere on the board
/RX1.P: C18.2; also elsewhere on the board
/RX2.N: C28.2; also elsewhere on the board
/RX2.P: C27.2; also elsewhere on the board
/RX3.N: C37.2; also elsewhere on the board
/RX3.P: C36.2; also elsewhere on the board
/~VIO_GOOD: R18.2, R25.2, R32.2; also elsewhere on the board
GND: C20.2, C21.2, C22.2, C29.2, C30.2, C31.2, C38.2, C39.2, C40.2, J2.2 (Ext), J3.2 (Ext), J4.2 (Ext), R14.2, R15.1, R17.2, R21.2, R22.1, R24.2, R28.2, R29.1, R31.2, U2.1 (VEE), U2.4 (VEE), U2.9 (VEE), U2.12 (VEE), U2.17 (EP), U3.1 (VEE), U3.4 (VEE), U3.9 (VEE), U3.12 (VEE), U3.17 (EP), U4.1 (VEE), U4.4 (VEE), U4.9 (VEE), U4.12 (VEE), U4.17 (EP); also elsewhere on the board
unnamed: C14.2, C15.1, L2.2, R13.2, R14.1
unnamed: C16.1, R15.2
unnamed: C23.2, C24.1, L3.2, R20.2, R21.1
unnamed: C25.1, R22.2
unnamed: C32.2, C33.1, L4.2, R27.2, R28.1
unnamed: C34.1, R29.2
unnamed: D3.2 (A), R16.2
unnamed: D4.2 (A), R23.2
unnamed: D5.2 (A), R30.2
unnamed: C14.1, J2.1 (In), L2.1, R13.1
unnamed: C23.1, J3.1 (In), L3.1, R20.1
unnamed: C32.1, J4.1 (In), L4.1, R27.1
unnamed: C17.1, U2.5 (AEC+)
unnamed: C17.2, U2.6 (AEC-)
unnamed: C16.2, U2.3 (SDI#)
unnamed: C15.2, U2.2 (SDI)
unnamed: C26.1, U3.5 (AEC+)
unnamed: C26.2, U3.6 (AEC-)
unnamed: C25.2, U3.3 (SDI#)
unnamed: C24.2, U3.2 (SDI)
unnamed: C35.1, U4.5 (AEC+)
unnamed: C35.2, U4.6 (AEC-)
unnamed: C34.2, U4.3 (SDI#)
unnamed: C33.2, U4.2 (SDI)

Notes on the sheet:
Decoupling
Input Active
BYPASS needs to be pulled down to enable EQ. MUTE needs to be tied to GND to enable output. MUTE can be tied to CD to mute while no input.
